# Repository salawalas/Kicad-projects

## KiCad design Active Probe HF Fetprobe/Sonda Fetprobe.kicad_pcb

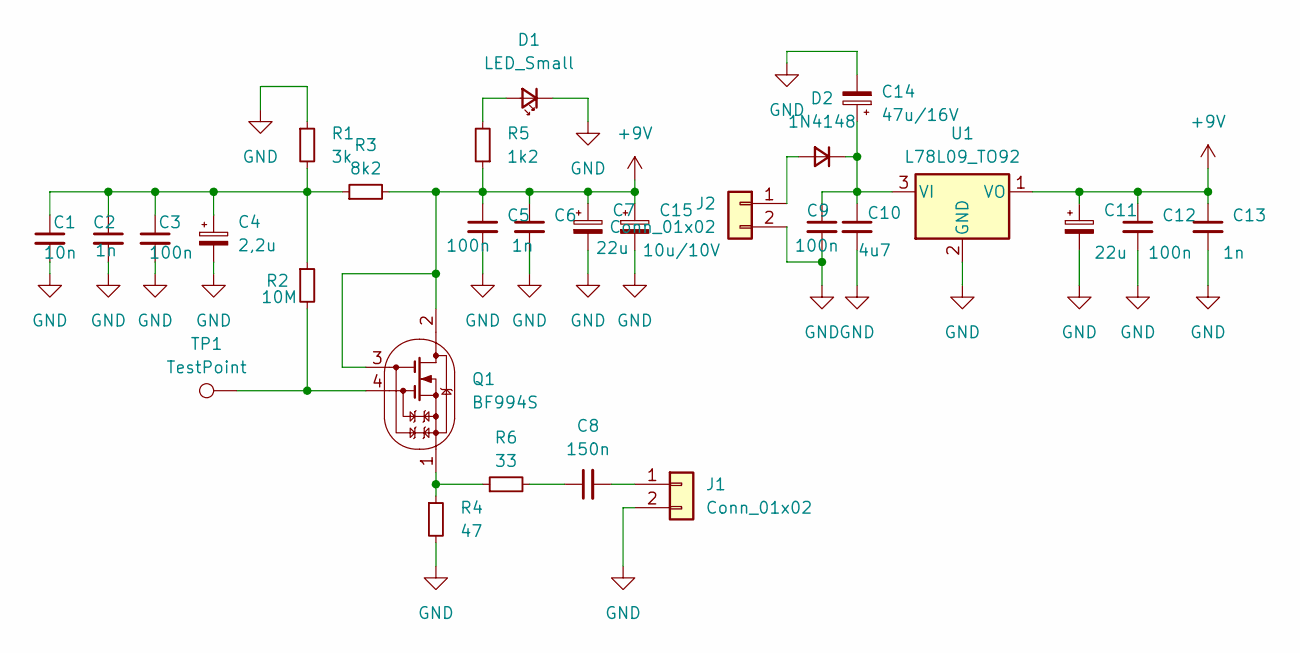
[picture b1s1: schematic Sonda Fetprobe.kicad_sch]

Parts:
C1: 10n; C_0805_2012Metric
C2, C6, C13: 1n; C_0805_2012Metric
C3, C5, C9, C12: 100n; C_0805_2012Metric
C4: 2,2u; C_1206_3216Metric
C7, C11: 22u; C_1206_3216Metric
C8: 150n; C_0805_2012Metric
C10: 4u7; C_1206_3216Metric
C14: 47u/16V; CP_EIA-7343-43_Kemet-X
C15: 10u/10V; CP_EIA-3528-12_Kemet-T
D1: LED_Small; LED_1206_3216Metric
D2: 1N4148; D_MiniMELF
J1: Conn_01x02; PinHeader_1x02_P2.54mm_Vertical
J2: Conn_01x02; JST_PH_B2B-PH-K_1x02_P2.00mm_Vertical
Q1: BF994S; SOT-143
R1: 3k; R_0805_2012Metric
R2: 10M; R_0805_2012Metric
R3: 8k2; R_0805_2012Metric
R4: 47; R_0805_2012Metric
R5: 1k2; R_0805_2012Metric
R6: 33; R_0805_2012Metric
TP1: TestPoint; PinHeader_1x01_P2.54mm_Vertical
U1: L78L09_TO92; TO-92_Horizontal1

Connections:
+9V: C5.1, C6.1, C7.1, C11.1, C12.1, C13.1, C15.1, Q1.2 (D), Q1.3 (G2), R3.2, R5.1, U1.1 (VO)
GND: C1.2, C2.2, C3.2, C4.2, C5.2, C6.2, C7.2, C9.2, C10.2, C11.2, C12.2, C13.2, C14.2, C15.2, D1.1 (K), J1.2, J2.2, R1.1, R4.2, U1.2 (GND)
unnamed: C1.1, C2.1, C3.1, C4.1, R1.2, R2.1, R3.1
unnamed: C8.1, R6.2
unnamed: D1.2 (A), R5.2
unnamed: D2.2 (A), J2.1
unnamed: C9.1, C10.1, C14.1, D2.1 (K), U1.3 (VI)
unnamed: C8.2, J1.1
unnamed: Q1.4 (G1), R2.2, TP1.1
unnamed: Q1.1 (S), R4.1, R6.1

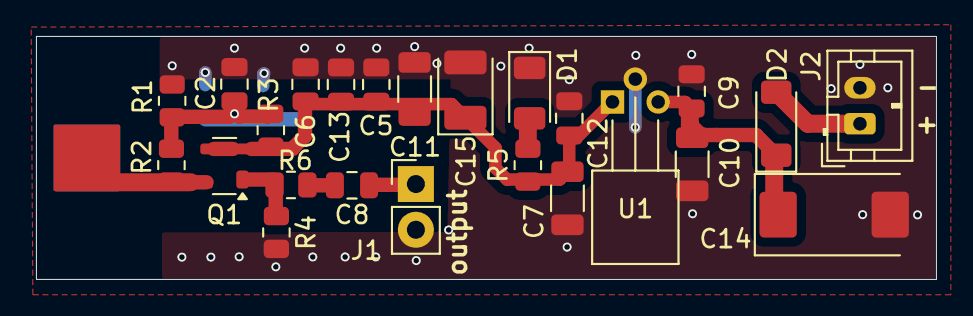
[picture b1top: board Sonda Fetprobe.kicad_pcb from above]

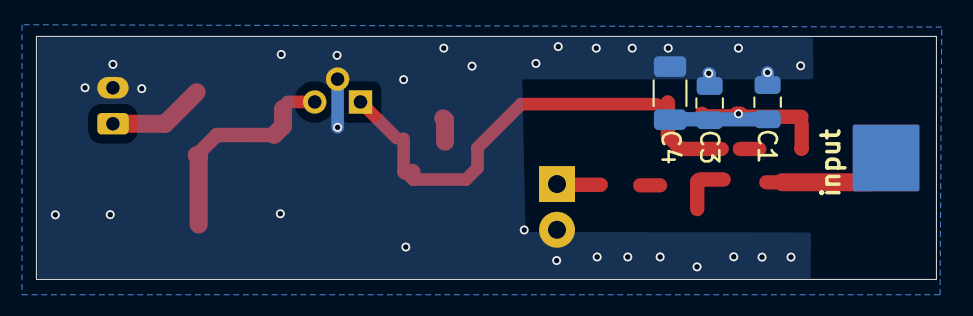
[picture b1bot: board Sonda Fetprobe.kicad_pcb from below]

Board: 6 copper layers, 50.0 x 13.5 mm, 27 parts (3 on the bottom side), 10 nets.

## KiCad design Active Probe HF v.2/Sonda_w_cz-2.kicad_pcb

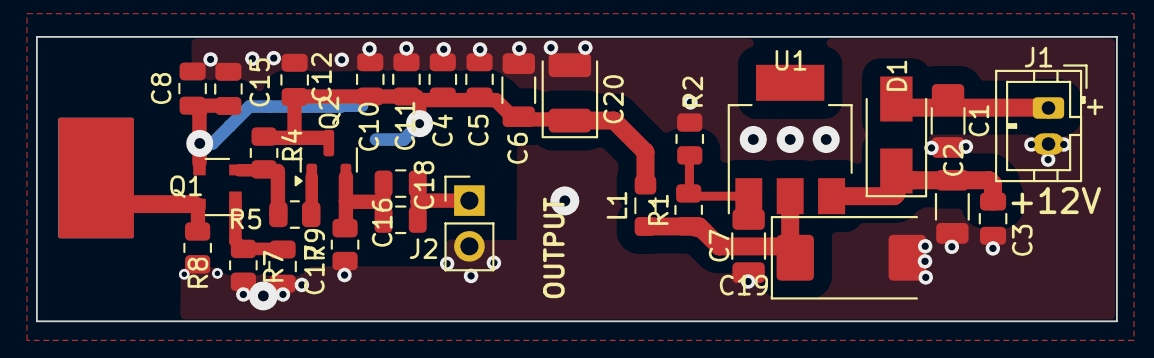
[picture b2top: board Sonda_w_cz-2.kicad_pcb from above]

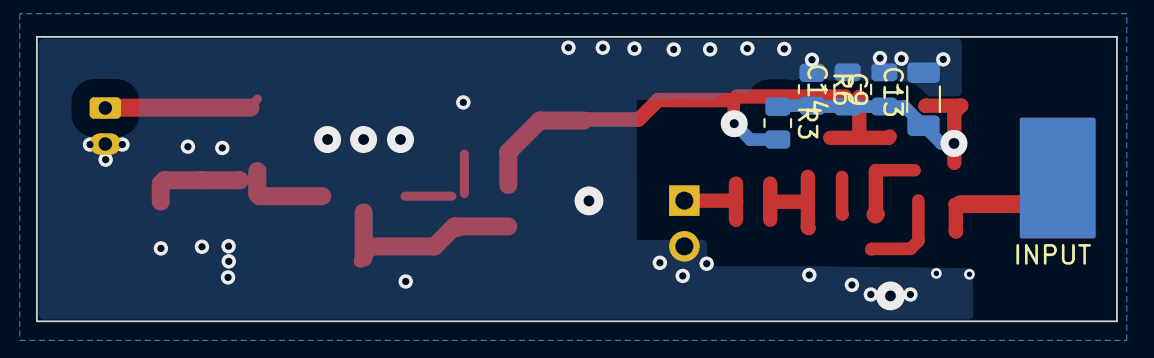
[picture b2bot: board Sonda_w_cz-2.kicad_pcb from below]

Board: 2 copper layers, 60.0 x 15.8 mm, 36 parts (5 on the bottom side), 13 nets.

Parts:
C1: 100n; C_1206_3216Metric
C2: 1u; C_1206_3216Metric
C3, C5, C11, C17: 100n; C_0805_2012Metric
C4: 4.7u; C_0805_2012Metric
C6, C7: 10u/12V; C_1206_3216Metric
C8, C14: 10n; C_0805_2012Metric
C9, C10, C12, C15, C16: 1n; C_0805_2012Metric
C13: 10u; C_1206_3216Metric
C18: 330n; C_0805_2012Metric
C19: 47u/16V; CP_EIA-7343-43_Kemet-X
C20: 10u/16V; CP_EIA-3528-12_Kemet-T
D1: US1M; D_SMA
J1: Conn_01x02_Female; JST_PH_B2B-PH-K_1x02_P2.00mm_Vertical
J2: Conn_01x02_Female; PinHeader_1x02_P2.54mm_Vertical
L1: 2u; L_0805_2012Metric_Pad1.05x1.20mm_HandSolder
Q1: BF994S; SOT-143
Q2: BFR93A; SOT-23
R1: 240; R_0805_2012Metric
R2, R4: 1k3; R_0805_2012Metric
R3, R6: 10k; R_0805_2012Metric
R5: 22; R_0805_2012Metric
R7: 51; R_0805_2012Metric
R8: 10M; R_0805_2012Metric
R9: 160; R_0805_2012Metric
U1: AMS1117; SOT-223-3_TabPin2

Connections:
+8V: C4.1, C5.1, C6.1, C10.1, C11.1, C12.1, C20.1, L1.2, Q2.3 (C), R3.2, R4.2
+11.4V: C2.1, C3.1, D1.1 (K), U1.3 (VI)
+12V: C1.1, D1.2 (A), J1.1
GND: C1.2, C2.2, C3.2, C4.2, C5.2, C6.2, C7.2, C8.2, C9.2, C10.2, C11.2, C12.2, C13.2, C14.2, C15.2, C17.2, C19.2, C20.2, J1.2, J2.2, R2.2, R6.1, R7.1, R8.1, R9.1
unnamed: C16.2, C18.2, J2.1
unnamed: Q1.2 (D), R4.1, R5.2
unnamed: Q1.4 (G1), R8.2
unnamed: C8.1, C9.1, C13.1, C14.1, C15.1, Q1.3 (G2), R3.1, R6.2
unnamed: C17.1, Q1.1 (S), R7.2
unnamed: Q2.1 (B), R5.1
unnamed: C16.1, C18.1, Q2.2 (E), R9.2
unnamed: C7.1, R1.2, R2.1, U1.1 (ADJ)
unnamed: C19.1, L1.1, R1.1, U1.2 (VO)

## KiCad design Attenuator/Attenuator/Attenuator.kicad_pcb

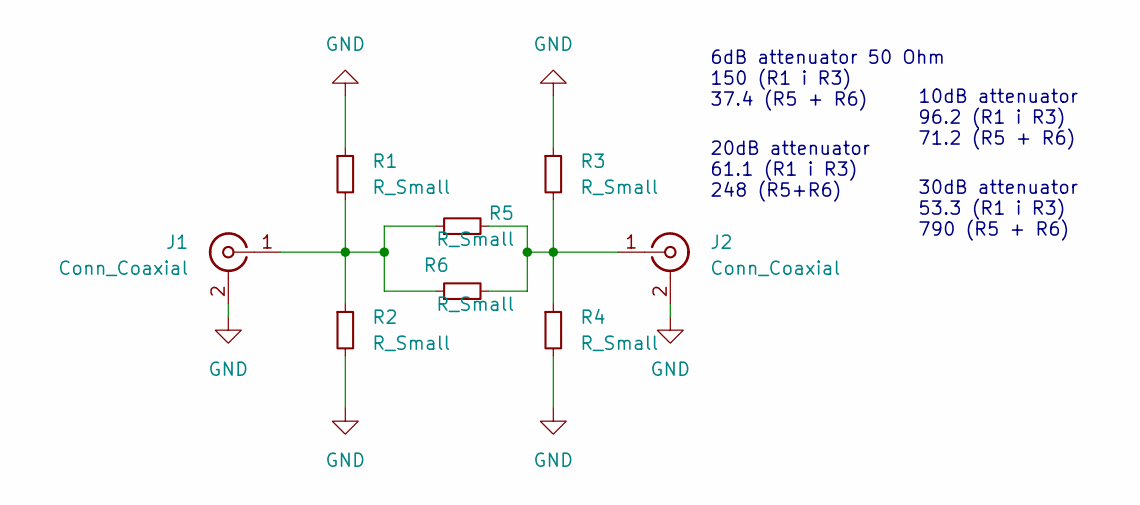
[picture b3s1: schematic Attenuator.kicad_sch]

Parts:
J1, J2: Conn_Coaxial; SMA_Molex_73251-2120_EdgeMount_Horizontal
R1, R2, R3, R4, R5, R6: R_Small; R_Axial_DIN0207_L6.3mm_D2.5mm_P10.16mm_Horizontal

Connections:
GND: J1.2 (Ext), J2.2 (Ext), R1.1, R2.2, R3.1, R4.2
unnamed: J1.1 (In), R1.2, R2.1, R5.1, R6.1
unnamed: J2.1 (In), R3.2, R4.1, R5.2, R6.2

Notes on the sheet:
6dB attenuator 50 Ohm 150 (R1 i R3) 37.4 (R5 + R6)
10dB attenuator 96.2 (R1 i R3) 71.2 (R5 + R6)
20dB attenuator 61.1 (R1 i R3) 248 (R5+R6)
30dB attenuator 53.3 (R1 i R3) 790 (R5 + R6)

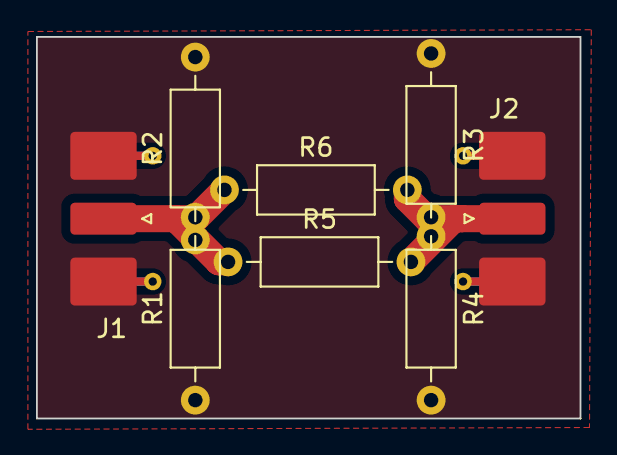
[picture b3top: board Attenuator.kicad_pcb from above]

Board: 2 copper layers, 30.2 x 21.2 mm, 8 parts (0 on the bottom side), 3 nets.

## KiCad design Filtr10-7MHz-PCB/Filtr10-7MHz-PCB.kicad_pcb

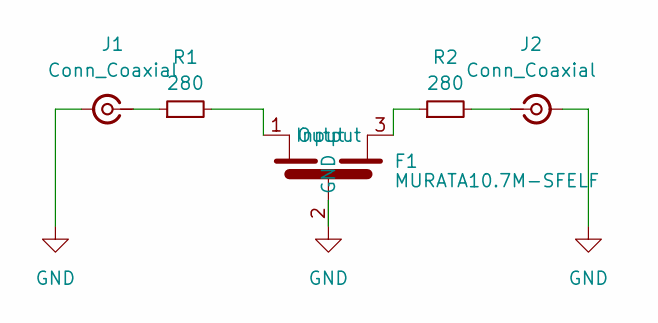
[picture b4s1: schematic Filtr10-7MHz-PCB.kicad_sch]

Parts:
F1: MURATA10.7M-SFELF; SFELF10M7-MURATA
J1, J2: Conn_Coaxial; SMA_Molex_73251-1153_EdgeMount_Horizontal
R1, R2: 280; R_0805_2012Metric_Pad1.20x1.40mm_HandSolder

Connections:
GND: F1.2 (GND), J1.2 (Ext), J2.2 (Ext)
unnamed: F1.1 (Input), R1.2
unnamed: F1.3 (Output), R2.1
unnamed: J1.1 (In), R1.1
unnamed: J2.1 (In), R2.2

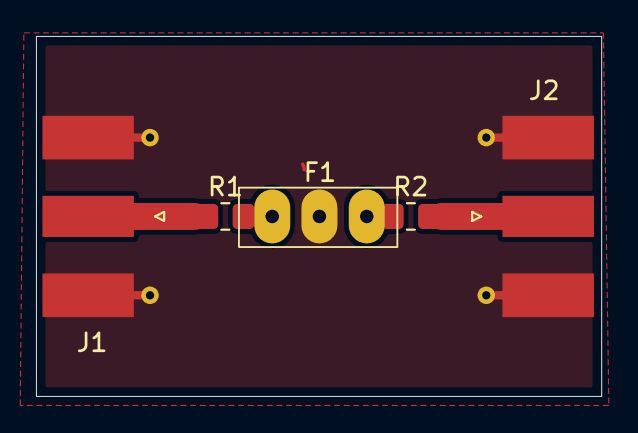
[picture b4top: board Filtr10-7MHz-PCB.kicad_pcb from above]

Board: 2 copper layers, 31.4 x 20.0 mm, 5 parts (0 on the bottom side), 5 nets.
